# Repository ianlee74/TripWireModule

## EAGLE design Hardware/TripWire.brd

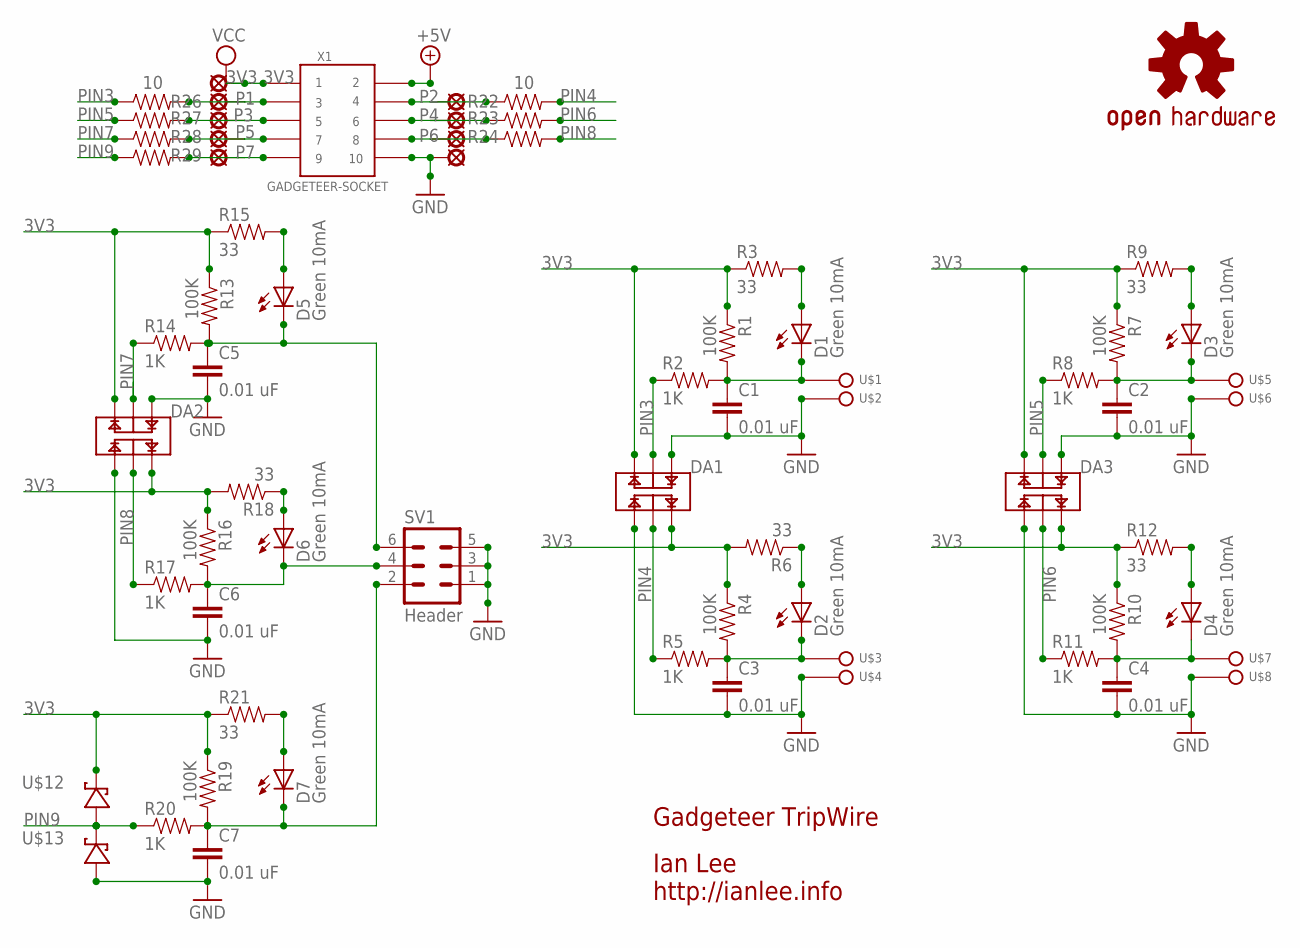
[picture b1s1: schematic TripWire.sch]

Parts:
3V3: LSP11
C1, C2, C3, C4, C5, C6, C7: 0.01 uF; 0603-CAP
D1, D2, D3, D4, D5, D6, D7: Green 10mA; LED-0603
DA1, DA2, DA3: BAT54SDW; SOT-363
GND: LSP11
LOGO1: OSHW-LOGOM; OSHW-LOGO-M
P1, P2, P3, P4, P5, P6, P7: LSP11
R1, R4, R7, R10, R13, R16, R19: 100K; 0603-RES
R2, R5, R8, R11, R14, R17, R20: 1K; 0603-RES
R3, R6, R9, R12, R15, R18, R21: 33; 0603-RES
R22, R23, R24, R26, R27, R28, R29: 10; 0603-RES
SV1: Header; MA03-2
U$1, U$2, U$3, U$4, U$5, U$6, U$7, U$8: SPADE-TERMINALPTH; SPADE-TERMINAL
U$12, U$13: BAT42-SCHOTTKY-DIODE; SOD-523F
X1: GADGETEER-SOCKET; 2X5_1.27MM

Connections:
3V3: 3V3.MP, DA1.P$1 (C2), DA1.P$4 (C1), DA2.P$1 (C2), DA2.P$4 (C1), DA3.P$1 (C2), DA3.P$4 (C1), R1.1, R3.1, R4.1, R6.2, R7.1, R9.1, R10.1, R12.1, R13.1, R15.1, R16.1, R18.2, R19.1, R21.1, U$12.P$1, X1.1
+5V: X1.2
GND: C1.2, C2.2, C3.2, C4.2, C5.2, C6.2, C7.2, DA1.P$2 (A2), DA1.P$3 (A1), DA2.P$2 (A2), DA2.P$3 (A1), DA3.P$2 (A2), DA3.P$3 (A1), GND.MP, SV1.1, SV1.3, SV1.5, U$2.P$1, U$4.P$1, U$6.P$1, U$8.P$1, U$13.P$2, X1.10
unnamed: D1.A, R3.2
unnamed: C3.1, D2.C, R4.2, R5.2, U$3.P$1
unnamed: D2.A, R6.1
unnamed: C2.1, D3.C, R7.2, R8.2, U$5.P$1
unnamed: D3.A, R9.2
unnamed: C7.1, D7.C, R19.2, R20.2, SV1.2
unnamed: D4.A, R12.2
unnamed: C4.1, D4.C, R10.2, R11.2, U$7.P$1
unnamed: C6.1, D6.C, R16.2, R17.2, SV1.4
unnamed: D7.A, R21.2
unnamed: C1.1, D1.C, R1.2, R2.2, U$1.P$1
unnamed: D6.A, R18.1
unnamed: D5.A, R15.2
unnamed: C5.1, D5.C, R13.2, R14.2, SV1.6
unnamed: P2.MP, R22.1, X1.4
unnamed: P4.MP, R23.1, X1.6
unnamed: P6.MP, R24.1, X1.8
unnamed: P1.MP, R26.2, X1.3
unnamed: P3.MP, R27.2, X1.5
unnamed: P5.MP, R28.2, X1.7
unnamed: P7.MP, R29.2, X1.9
PIN3: DA1.P$5 (AC2), R2.1, R26.1
PIN4: DA1.P$0 (AC1), R5.1, R22.2
PIN5: DA3.P$5 (AC2), R8.1, R27.1
PIN6: DA3.P$0 (AC1), R11.1, R23.2
PIN7: DA2.P$5 (AC2), R14.1, R28.1
PIN8: DA2.P$0 (AC1), R17.1, R24.2
PIN9: R20.1, R29.1, U$12.P$2, U$13.P$1

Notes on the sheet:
Gadgeteer TripWire
Ian Lee http://ianlee.info

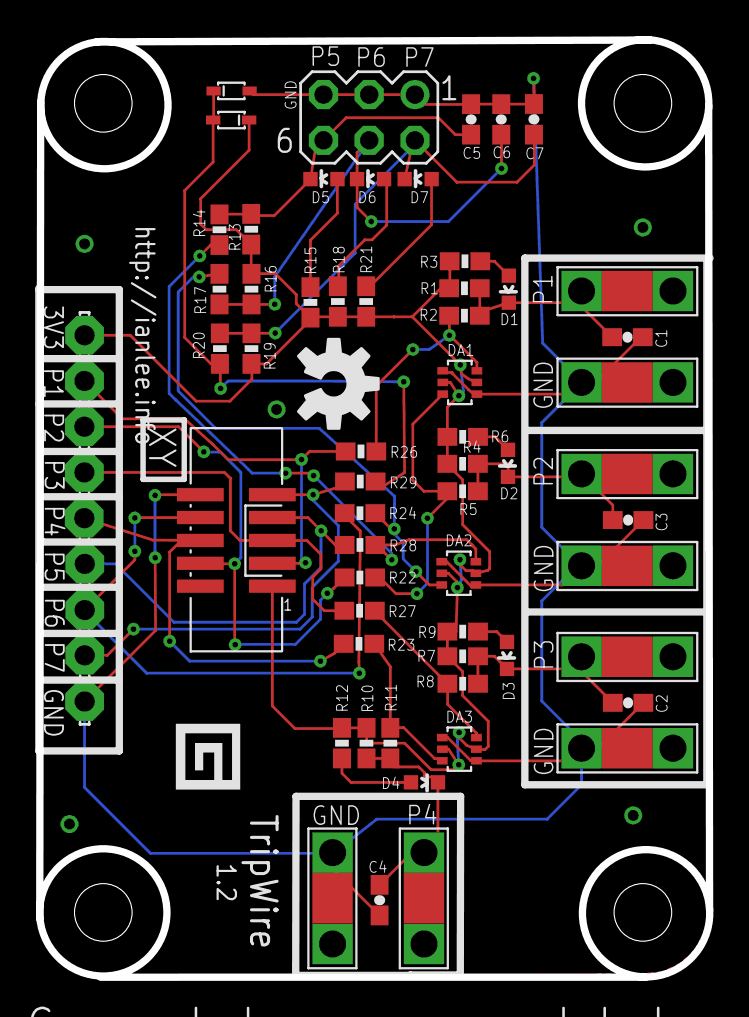
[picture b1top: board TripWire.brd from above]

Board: 2 copper layers, 37.2 x 52.1 mm, 67 parts (0 on the bottom side), 30 nets.

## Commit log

2013-01-12 Initial commit.
2013-01-12 Created projects using Builders templates.
2013-01-21 Removed autosave files and add to .gitignore.
2013-01-21 Removed autosave files.
2013-01-23 Routing 1st draft.
2013-01-24 All DRC checks passed.
2013-01-24 Added LED enable junction pads.
2013-01-24 Added XY socket label.
2013-01-25 v1.0 finalized and shipped off to DFRobot.
2013-01-28 Adjusted spade connector placement to give female connectors proper clearance. Added trip wire logo to back.
2013-01-29 Added pin breakout for non-Gadgeteer use.
2013-01-29 Updated OSHW logo.
2013-02-02 Added pin protection diodes.
2013-02-03 WiP - adding TVS diode array.
2013-02-17 Adjusted text sizes & placement.
2013-02-20 Sent v1.1 to DFRobot.com
2013-03-05 Moved 3V3 label to the front of the board.
2013-03-05 Relocated the G logo.
2013-03-05 Added TripWireTester app.
2013-03-07 Changed the OSHW logo to use the SparkFun medium one.
2013-03-21 Merged 3V3 & 3V3_B nets.
2013-05-20 Added 100 Ohm resistors to IO pins.
2013-05-20 Started replacing TVS with BAT54S diode arrays.
2013-05-21 Downgraded to Eagle 6.1.0. Added Schottky circuit protection and signal filtering capacitors.
2013-05-21 Created BAT54SDW diode array part.
2013-05-22 Replaced all transistor pairs with BAT54SDW diode arrays.
2013-05-22 Replaced single diodes with BAT42 custom part.
2013-05-22 Resized board to start new routing.
2013-05-25 Re-routed and all CRC checks resolved.
2013-05-25 Moved C4.
2013-05-25 Adjusted 10ohm resistor layout.
2013-05-25 Re-centered logo.
2013-05-25 Moved OSHW logo.
2013-05-25 Adjusted font & silk around P4.
2013-05-25 Fixed bad connection on D6.
2013-05-25 Optimized some routes.
2013-05-26 Eliminated some vias.
2013-05-26 Added ground planes.
2013-05-26 Changed ground plane to be hatched.
2013-05-26 v1.2 CAM files created and shipped off to DFRobot.com
2013-06-23 Fixed 5mm spacing on mounting holes.
2015-06-02 Added 4.3 driver.

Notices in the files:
parts and their libraries:
SparkFun-LED: Licensing: CC v3.0 Share-Alike You are welcome to use this library for commercial purposes.
